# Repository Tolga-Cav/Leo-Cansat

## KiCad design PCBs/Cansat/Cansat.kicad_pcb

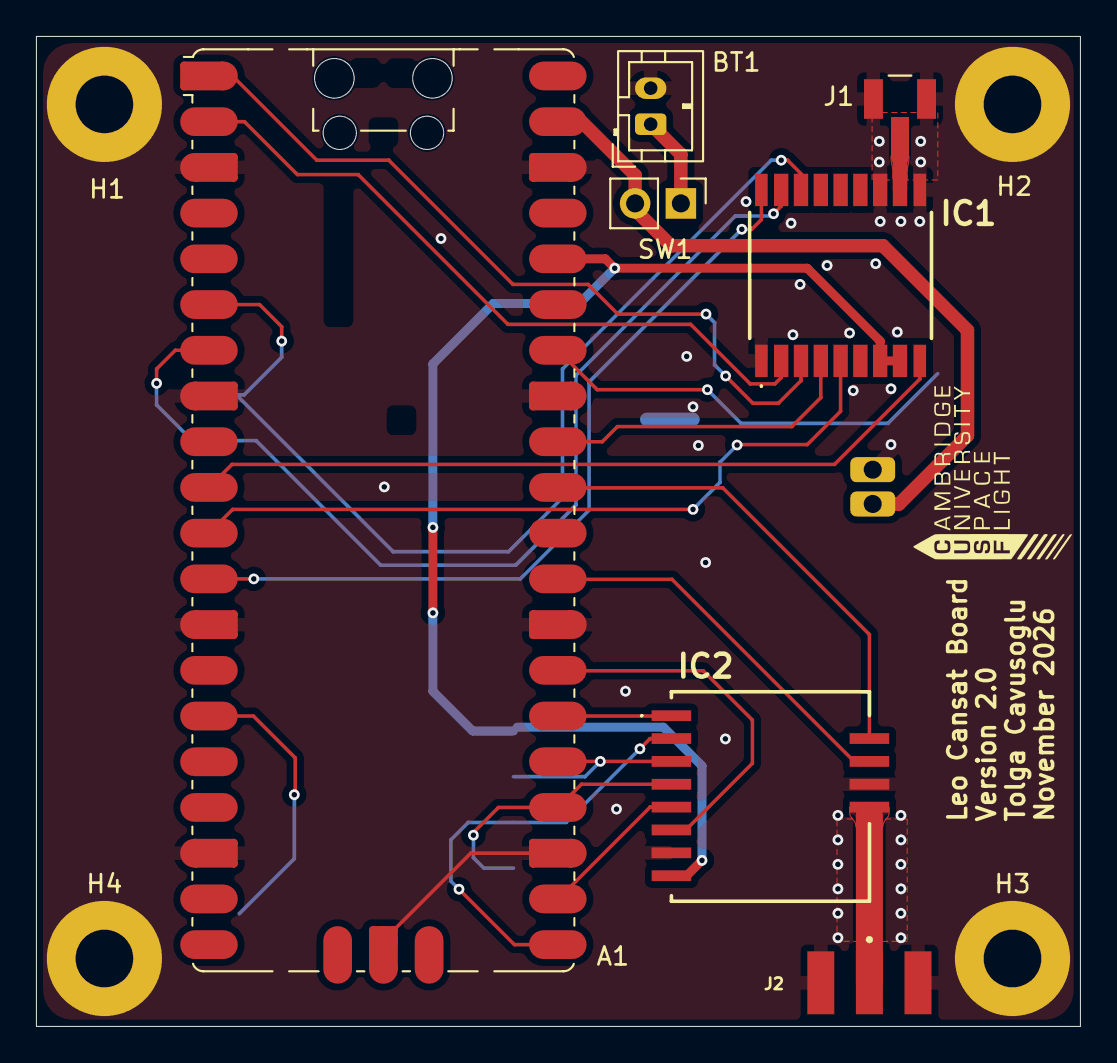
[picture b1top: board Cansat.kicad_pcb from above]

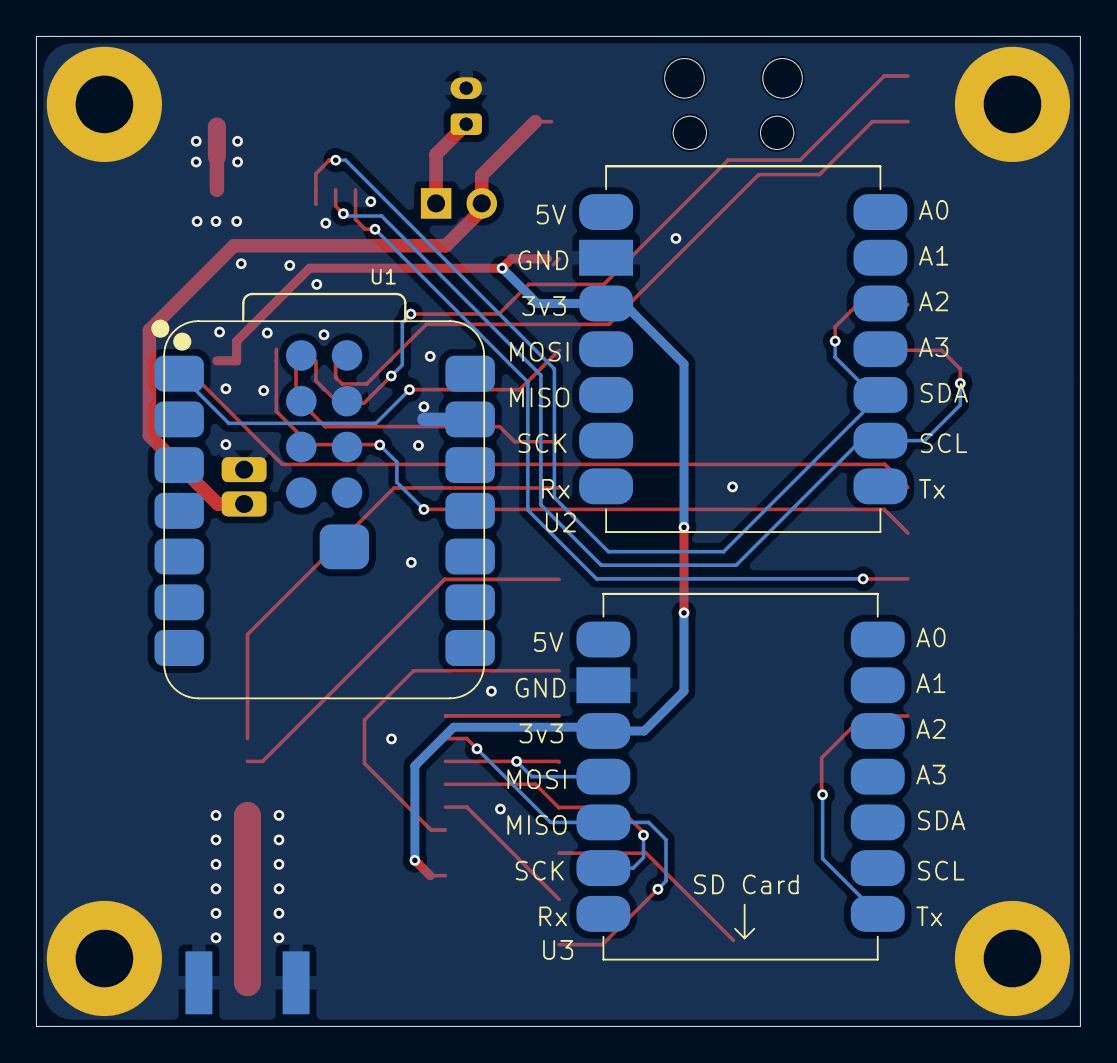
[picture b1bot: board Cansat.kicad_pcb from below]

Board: 2 copper layers, 58.0 x 55.0 mm, 14 parts (3 on the bottom side), 24 nets.

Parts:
A1: RaspberryPi_Pico; RaspberryPi_Pico_SMD_HandSolder
BT1: Battery; JST_PH_B2B-PH-K_1x02_P2.00mm_Vertical
H1, H2, H3, H4: MountingHole_Pad; MountingHole_3.2mm_M3_Pad
IC1: MAX-F10S-00B; MAXF10S00B
IC2: WIO SX-1262; wio sx1262
J1: Conn_Coaxial; HIROSE_U.FL-R-SMT_10_
J2: Conn_Coaxial; RFSOLUTIONS_CON-SMA-EDGE-S
SW1: SW_SPST; PinHeader_1x02_P2.54mm_Vertical
U1: Val**; XIAO-ESP32-S3-SMD
U2: Sensor BFF
U3: Microsd BFF

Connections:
+3.3V: A1.36 (3V3), IC1.7 (V_IO), IC1.8 (VCC), IC2.8 (VCC), U2.3 (3.3V), U3.3 (3.3V)
+BATT: A1.39 (VSYS), SW1.2 (B), U1.23 (VBAT)
/GPS EXINT: A1.11 (GPIO8), IC1.5 (EXTINT)
/GPS RST: A1.10 (GPIO7), IC1.9 (RESET_N)
/GPS SAFEBOOT_N: A1.12 (GPIO9), IC1.18 (SAFEBOOT_N)
/GPS TIMEPULSE: A1.32 (GPIO27_ADC1), IC1.4 (TIMEPULSE)
/LORA BUSY: A1.29 (GPIO22), IC2.11 (BUSY)
/LORA DIO1: A1.31 (GPIO26_ADC0), IC2.12 (DIO1)
/LORA NSS: A1.27 (GPIO21), IC2.6 (NSS)
/LORA RF SW: A1.26 (GPIO20), IC2.1 (RF_SW_)
/LORA RST: A1.22 (GPIO17), IC2.5 (NRST)
/MISO: A1.21 (GPIO16), IC2.2 (MISO), U3.5 (MISO)
/MOSI: A1.25 (GPIO19), IC2.3 (MOSI), U3.4 (MOSI)
/SCK: A1.24 (GPIO18), IC2.4 (SCK), U3.6 (SCK)
/SCL: A1.7 (GPIO5), IC1.17 (SCL), U2.9 (SCL)
/SD Card CS: A1.15 (GPIO11), U3.8 (Tx)
/SDA: A1.6 (GPIO4), IC1.16 (SDA), U2.10 (SDA)
/Shutter: A1.34 (GPIO28_ADC2), U1.1 (D0)
/UART Rx: A1.2 (GPIO1), IC1.2 (TXD)
/UART Tx: A1.1 (GPIO0), IC1.3 (RXD)
GND: A1.3 (GND), A1.8 (GND), A1.13 (GND), A1.18 (GND), A1.23 (GND), A1.28 (GND), A1.33 (AGND), A1.38 (GND), A1.D2 (GND), BT1.2 (-), H1.1 (1_1), H2.1 (1_1), H3.1 (1_1), H4.1 (1_1), IC1.1 (GND_1), IC1.10 (GND_2), IC1.12 (GND_3), IC2.7 (GND_1), IC2.10 (GND_2), J1.2 (Ext), J2.2 (Ext), U1.13 (GND), U1.18 (GND), U1.24 (GND), U2.2 (GND), U3.2 (GND)
unnamed: BT1.1 (+), SW1.1 (A)
unnamed: IC1.11 (RF_IN), J1.1 (In)
unnamed: IC2.9 (ANT), J2.1 (In)

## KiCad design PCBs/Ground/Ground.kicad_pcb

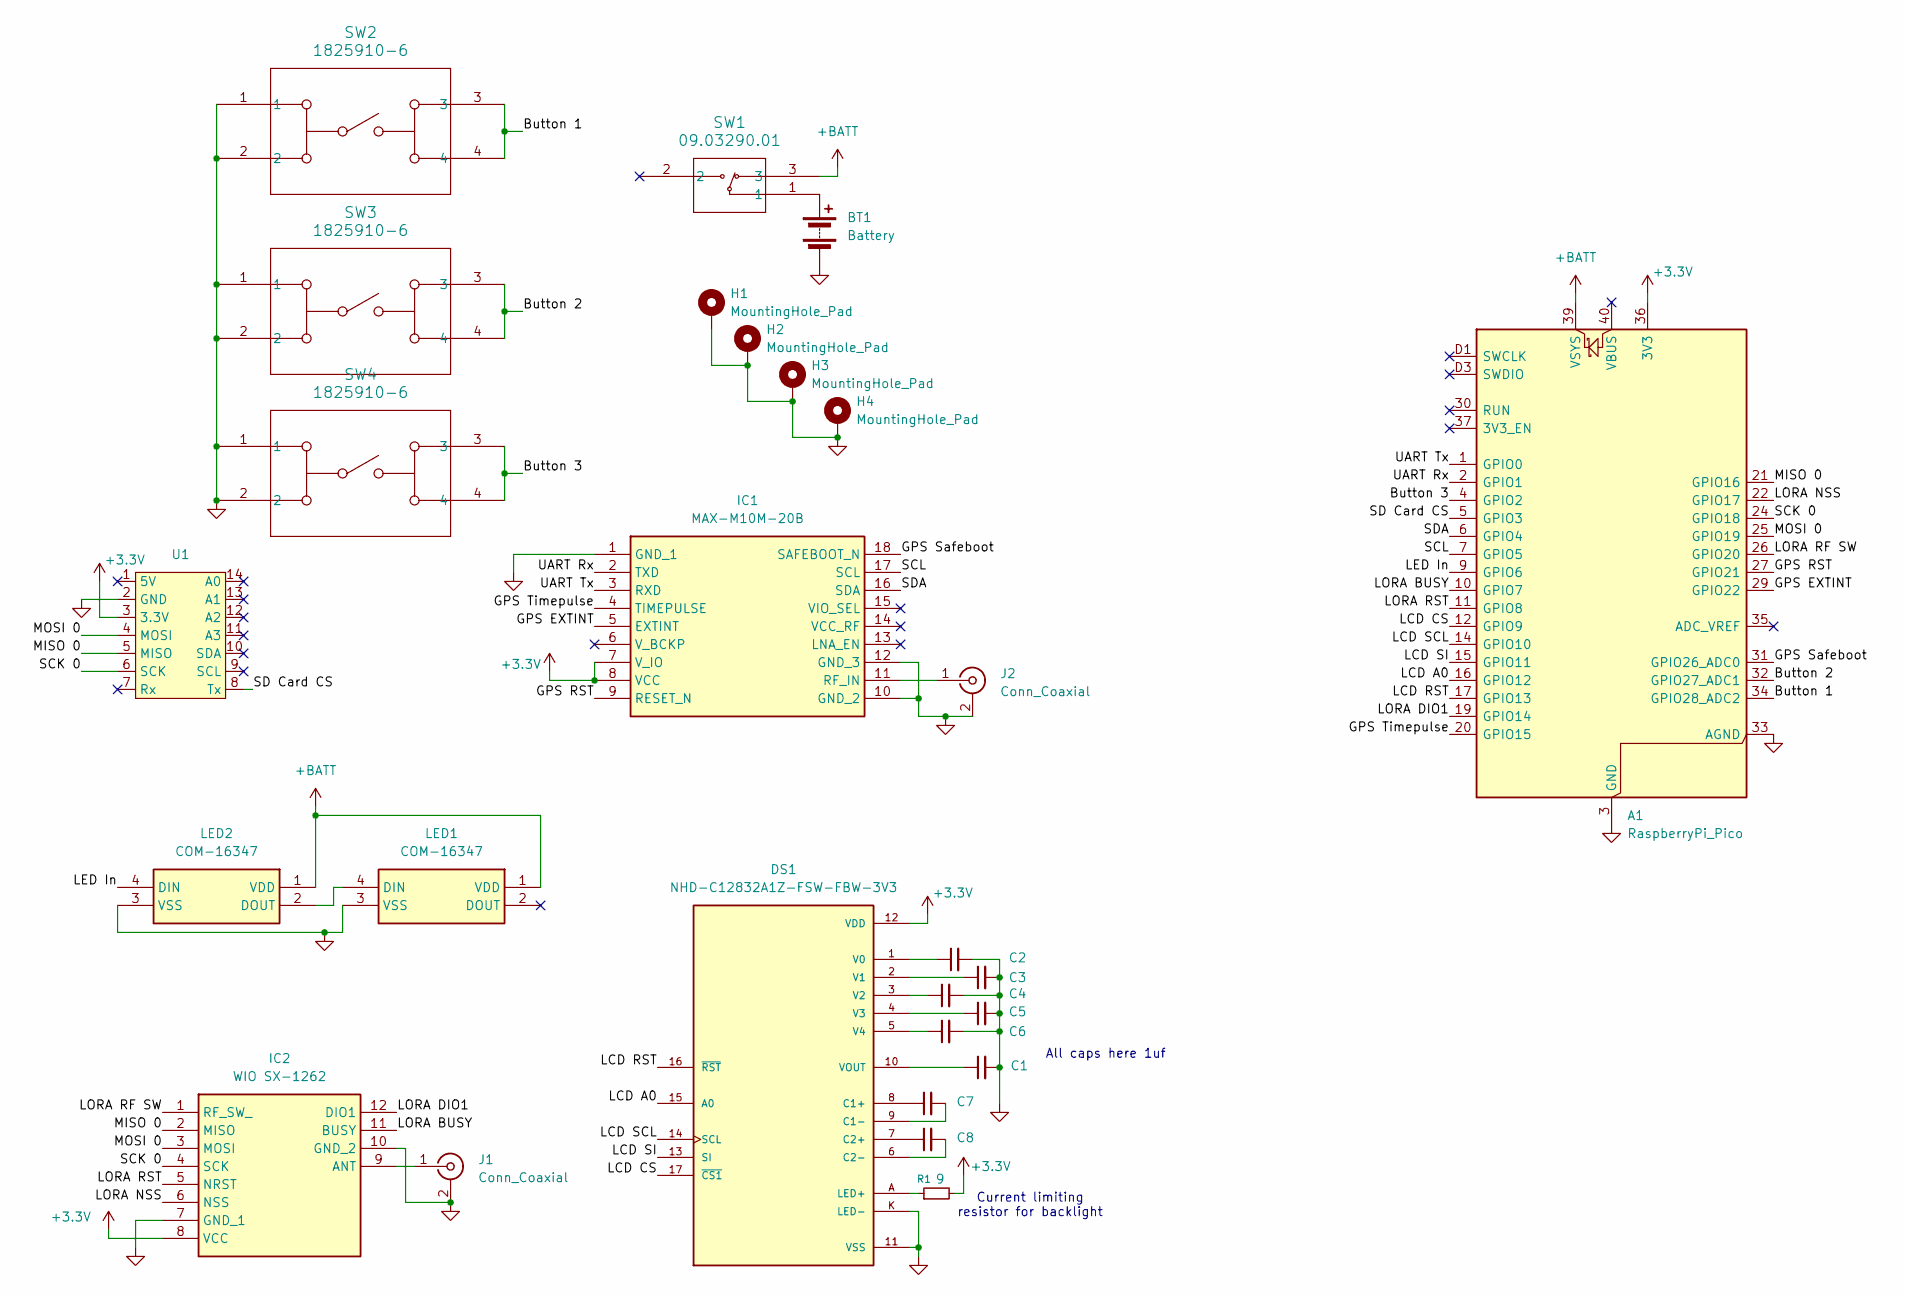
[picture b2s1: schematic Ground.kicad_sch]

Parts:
A1: RaspberryPi_Pico; RaspberryPi_Pico_SMD_HandSolder
BT1: Battery; JST_PH_B2B-PH-K_1x02_P2.00mm_Vertical
C1, C2, C3, C4, C5, C6, C7, C8: C_Small; C_0805_2012Metric_Pad1.18x1.45mm_HandSolder
DS1: NHD-C12832A1Z-FSW-FBW-3V3; LCD_NHD-C12832A1Z-FSW-FBW-3V3; MPN NHD-C12832A1Z-FSW-FBW-3V3
H1, H2, H3, H4: MountingHole_Pad; MountingHole_3.2mm_M3_DIN965_Pad
IC1: MAX-M10M-20B; MAXM10M20B; Manufacturer_Part_Number MAX-M10M-20B
IC2: WIO SX-1262; wio sx1262; Mouser Part Number 713-114993390
J1: Conn_Coaxial; RFSOLUTIONS_CON-SMA-EDGE-S
J2: Conn_Coaxial; HIROSE_U.FL-R-SMT_10_
LED1, LED2: COM-16347; COM16347; Mouser Part Number 474-COM-16347
R1: 9; R_0805_2012Metric_Pad1.20x1.40mm_HandSolder
SW1: 09.03290.01; 09.03290_EAO
SW2, SW3, SW4: 1825910-6; SW4_1825910-B_TEC
U1: Microsd BFF

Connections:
+3.3V: A1.36 (3V3), DS1.12 (VDD), IC1.7 (V_IO), IC1.8 (VCC), IC2.8 (VCC), R1.2, U1.3 (3.3V)
+BATT: A1.39 (VSYS), LED1.1 (VDD), LED2.1 (VDD), SW1.3
/Button 1: A1.34 (GPIO28_ADC2), SW2.3, SW2.4
/Button 2: A1.32 (GPIO27_ADC1), SW3.3, SW3.4
/Button 3: A1.4 (GPIO2), SW4.3, SW4.4
/GPS EXTINT: A1.29 (GPIO22), IC1.5 (EXTINT)
/GPS RST: A1.27 (GPIO21), IC1.9 (RESET_N)
/GPS Safeboot: A1.31 (GPIO26_ADC0), IC1.18 (SAFEBOOT_N)
/GPS Timepulse: A1.20 (GPIO15), IC1.4 (TIMEPULSE)
/LCD A0: A1.16 (GPIO12), DS1.15 (A0)
/LCD CS: A1.12 (GPIO9), DS1.17 (~CS1)
/LCD RST: A1.17 (GPIO13), DS1.16 (~RST)
/LCD SCL: A1.14 (GPIO10), DS1.14 (SCL)
/LCD SI: A1.15 (GPIO11), DS1.13 (SI)
/LED In: A1.9 (GPIO6), LED2.4 (DIN)
/LORA BUSY: A1.10 (GPIO7), IC2.11 (BUSY)
/LORA DIO1: A1.19 (GPIO14), IC2.12 (DIO1)
/LORA NSS: A1.22 (GPIO17), IC2.6 (NSS)
/LORA RF SW: A1.26 (GPIO20), IC2.1 (RF_SW_)
/LORA RST: A1.11 (GPIO8), IC2.5 (NRST)
/MISO 0: A1.21 (GPIO16), IC2.2 (MISO), U1.5 (MISO)
/MOSI 0: A1.25 (GPIO19), IC2.3 (MOSI), U1.4 (MOSI)
/SCK 0: A1.24 (GPIO18), IC2.4 (SCK), U1.6 (SCK)
/SCL: A1.7 (GPIO5), IC1.17 (SCL)
/SD Card CS: A1.5 (GPIO3), U1.8 (Tx)
/SDA: A1.6 (GPIO4), IC1.16 (SDA)
/UART Rx: A1.2 (GPIO1), IC1.2 (TXD)
/UART Tx: A1.1 (GPIO0), IC1.3 (RXD)
GND: A1.3 (GND), A1.8 (GND), A1.13 (GND), A1.18 (GND), A1.23 (GND), A1.28 (GND), A1.33 (AGND), A1.38 (GND), A1.D2 (GND), BT1.2 (-), C1.2, C2.2, C3.2, C4.2, C5.2, C6.2, DS1.11 (VSS), DS1.K (LED-), H1.1 (1_1), H2.1 (1_1), H3.1 (1_1), H4.1 (1_1), IC1.1 (GND_1), IC1.10 (GND_2), IC1.12 (GND_3), IC2.7 (GND_1), IC2.10 (GND_2), J1.2 (Ext), J2.2 (Ext), LED1.3 (VSS), LED2.3 (VSS), SW2.1, SW2.2, SW3.1, SW3.2, SW4.1, SW4.2, U1.2 (GND)
unnamed: BT1.1 (+), SW1.1
unnamed: C7.1, DS1.8 (C1+)
unnamed: C7.2, DS1.9 (C1-)
unnamed: C8.1, DS1.7 (C2+)
unnamed: C8.2, DS1.6 (C2-)
unnamed: DS1.A (LED+), R1.1
unnamed: C2.1, DS1.1 (V0)
unnamed: C3.1, DS1.2 (V1)
unnamed: C4.1, DS1.3 (V2)
unnamed: C5.1, DS1.4 (V3)
unnamed: C6.1, DS1.5 (V4)
unnamed: C1.1, DS1.10 (VOUT)
unnamed: IC1.11 (RF_IN), J2.1 (In)
unnamed: IC2.9 (ANT), J1.1 (In)
unnamed: LED1.4 (DIN), LED2.2 (DOUT)

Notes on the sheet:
Current limiting resistor for backlight
All caps here 1uf

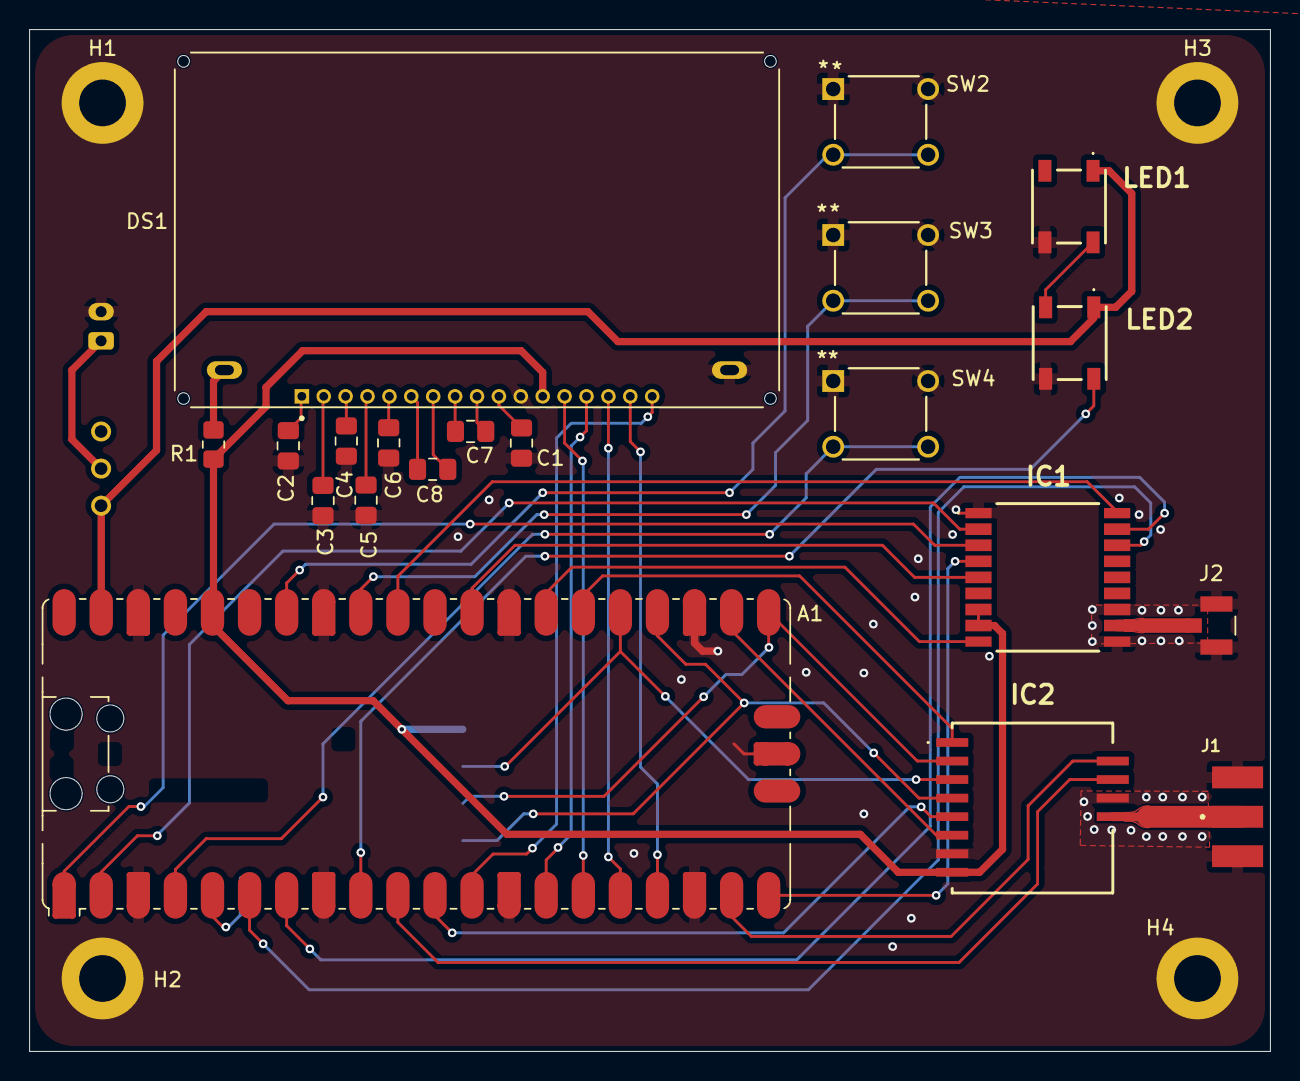
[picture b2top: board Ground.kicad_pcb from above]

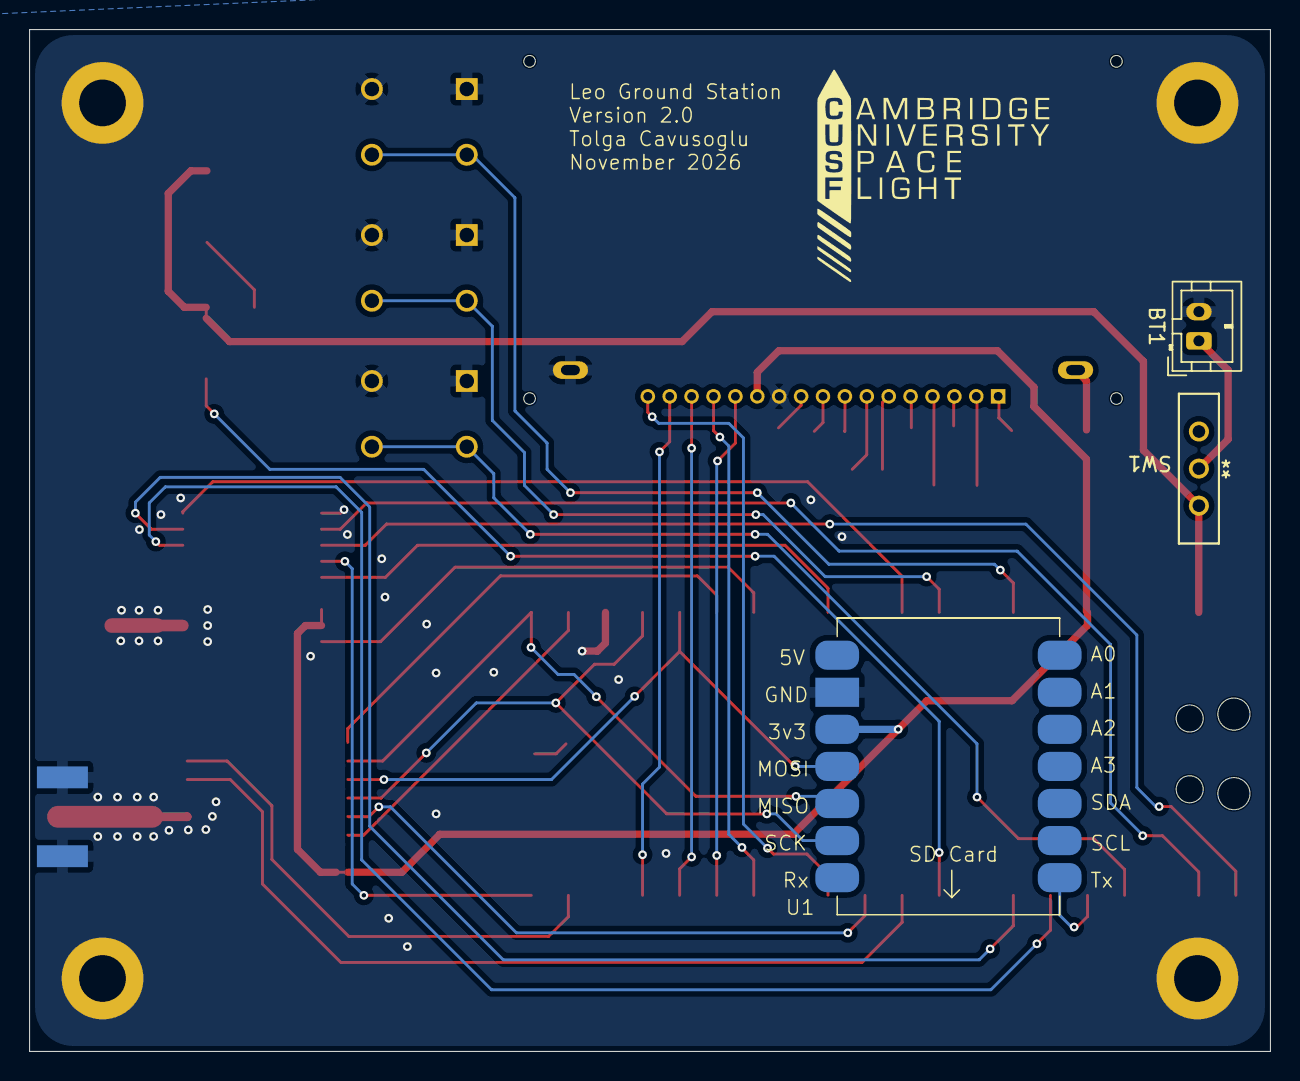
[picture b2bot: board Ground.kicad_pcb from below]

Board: 2 copper layers, 85.0 x 70.0 mm, 27 parts (3 on the bottom side), 44 nets.

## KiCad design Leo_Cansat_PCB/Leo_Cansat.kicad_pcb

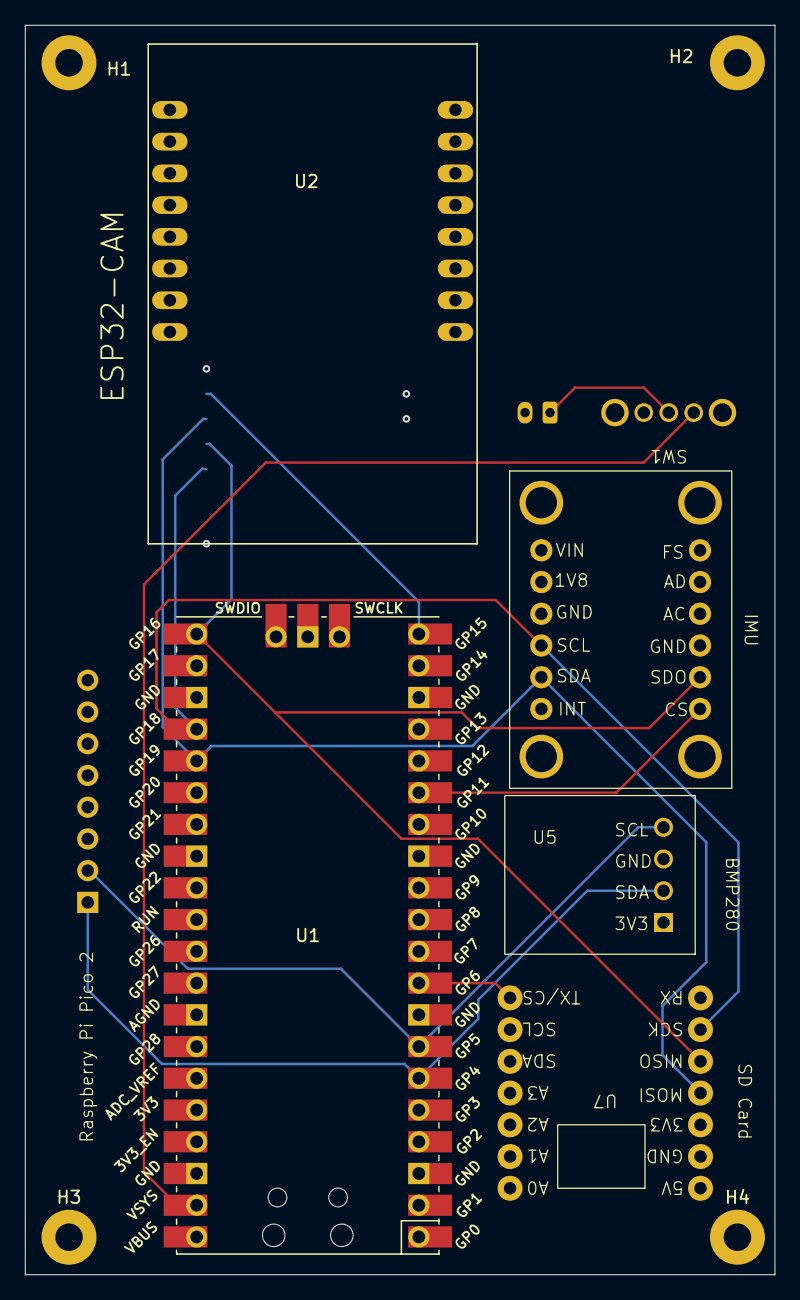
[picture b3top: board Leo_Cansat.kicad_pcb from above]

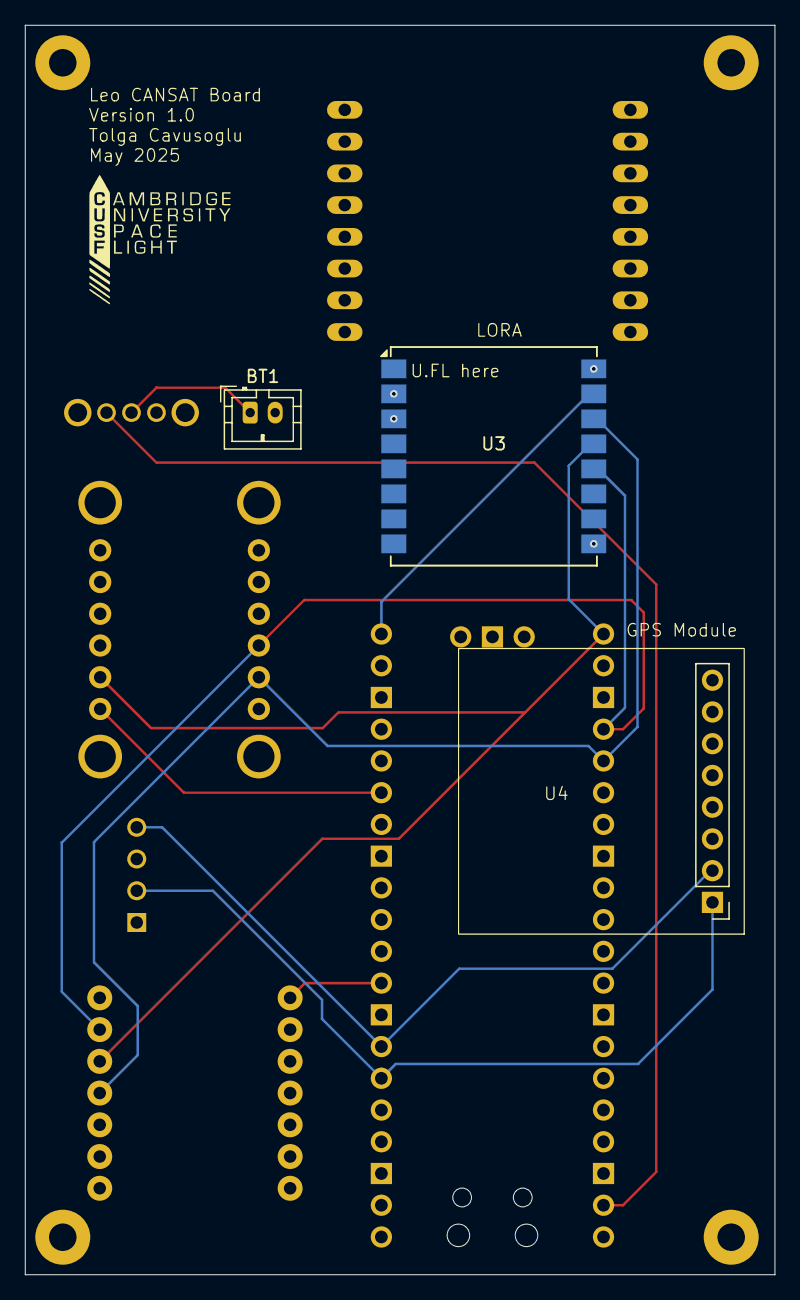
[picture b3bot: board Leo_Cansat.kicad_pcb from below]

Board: 4 copper layers, 60.0 x 100.0 mm, 13 parts (3 on the bottom side), 12 nets.

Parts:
BT1: Battery_Cell; JST_PH_B2B-PH-K_1x02_P2.00mm_Vertical
H1, H2, H3, H4: MountingHole_Pad; MountingHole_2.2mm_M2_Pad
SW1: SW_SPDT; SK-12D07
U1: Pico; RPi_Pico_SMD_TH
U2: ESP32-CAM
U3: Ai-Thinker-Ra-01; Ai-Thinker-Ra-01-LoRa
U4: MAX-M8Q-0-10 breakout board
U5: AHT20+BMP280
U6: ICM20948
U7: BFF SD Card

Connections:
+3V3: U1.36 (3V3), U2.P$16 (3V3), U3.3 (VDD), U4.8 (VCC), U5.4 (VCC), U6.7 (VIN), U7.3 (3V3)
/IMUCS: U1.15 (GPIO11), U6.1 (CS)
/LORACS: U1.20 (GPIO15), U3.15 (~NSS)
/MISO: U1.21 (GPIO16), U3.13 (MISO), U6.2 (SDO), U7.5 (MISO)
/MOSI: U1.25 (GPIO19), U3.14 (MOSI), U6.11 (SDA), U7.4 (MOSI)
/SCK: U1.24 (GPIO18), U3.12 (SCK), U6.10 (SCL), U7.6 (SCK)
/SCL: U1.7 (GPIO5), U4.2 (SCL), U5.1 (SCL)
/SDA: U1.6 (GPIO4), U4.1 (SDA), U5.3 (SDA)
/SDCS: U1.9 (GPIO6), U7.14 (CS)
GND: BT1.2 (-), H1.1, H2.1, H3.1, H4.1, U1.3 (GND), U1.8 (GND), U1.13 (GND), U1.18 (GND), U1.23 (GND), U1.28 (GND), U1.38 (GND), U1.42 (GND), U2.P$2 (GND), U3.2 (GND), U3.9 (GND), U3.16 (GND), U4.7 (GND), U5.2 (GND), U6.3 (GND), U7.2 (GND)
unnamed: BT1.1 (+), SW1.2 (B)
unnamed: SW1.1 (A), U1.39 (VSYS)

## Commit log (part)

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2025-06-21 Initial Commit
    First addition of all files to the repository.
2025-06-29 Updated GPS test code to reflect UART
2025-10-12 Some small cad changes
2025-10-17 CAD Updates
2025-10-26 Fixed uart Pins on GPS Test code
2025-11-16 Lora Testing
2025-11-16 Added Lora Library
2025-11-16 Correct Lora Library
2025-11-16 Lora configuration test
2025-11-23 Further LoRa Testing
2026-02-02 Implement ESP-32 Camera Test
2026-02-22 Fix pin definitions in library
2026-02-22 Finalize ESP 32 Cam code
2026-03-14 Started main code loop for cansat
2026-03-15 Minor Edits
